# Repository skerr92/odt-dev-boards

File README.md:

# odt-dev-boards
repo for all the development boards for ODT

# Usage of Design Files

At Oak Development Technologies, we believe in open source hardware and software. To make this happen, we willingly publish the schematic and board files to 
all of our designs. With this in mind, we did take time to make these designs and share them with you and hope that you respect the MIT License we've attached herein to this repository.

Additionally, while we share these designs freely, making them isn't free. Purchasing these boards and designs from our store helps us continue to offer these designs free of charge.

Please help support the open source community and our contributions through sharing our mission with others and where possible, purchasing the hardware we cheerfully build for you

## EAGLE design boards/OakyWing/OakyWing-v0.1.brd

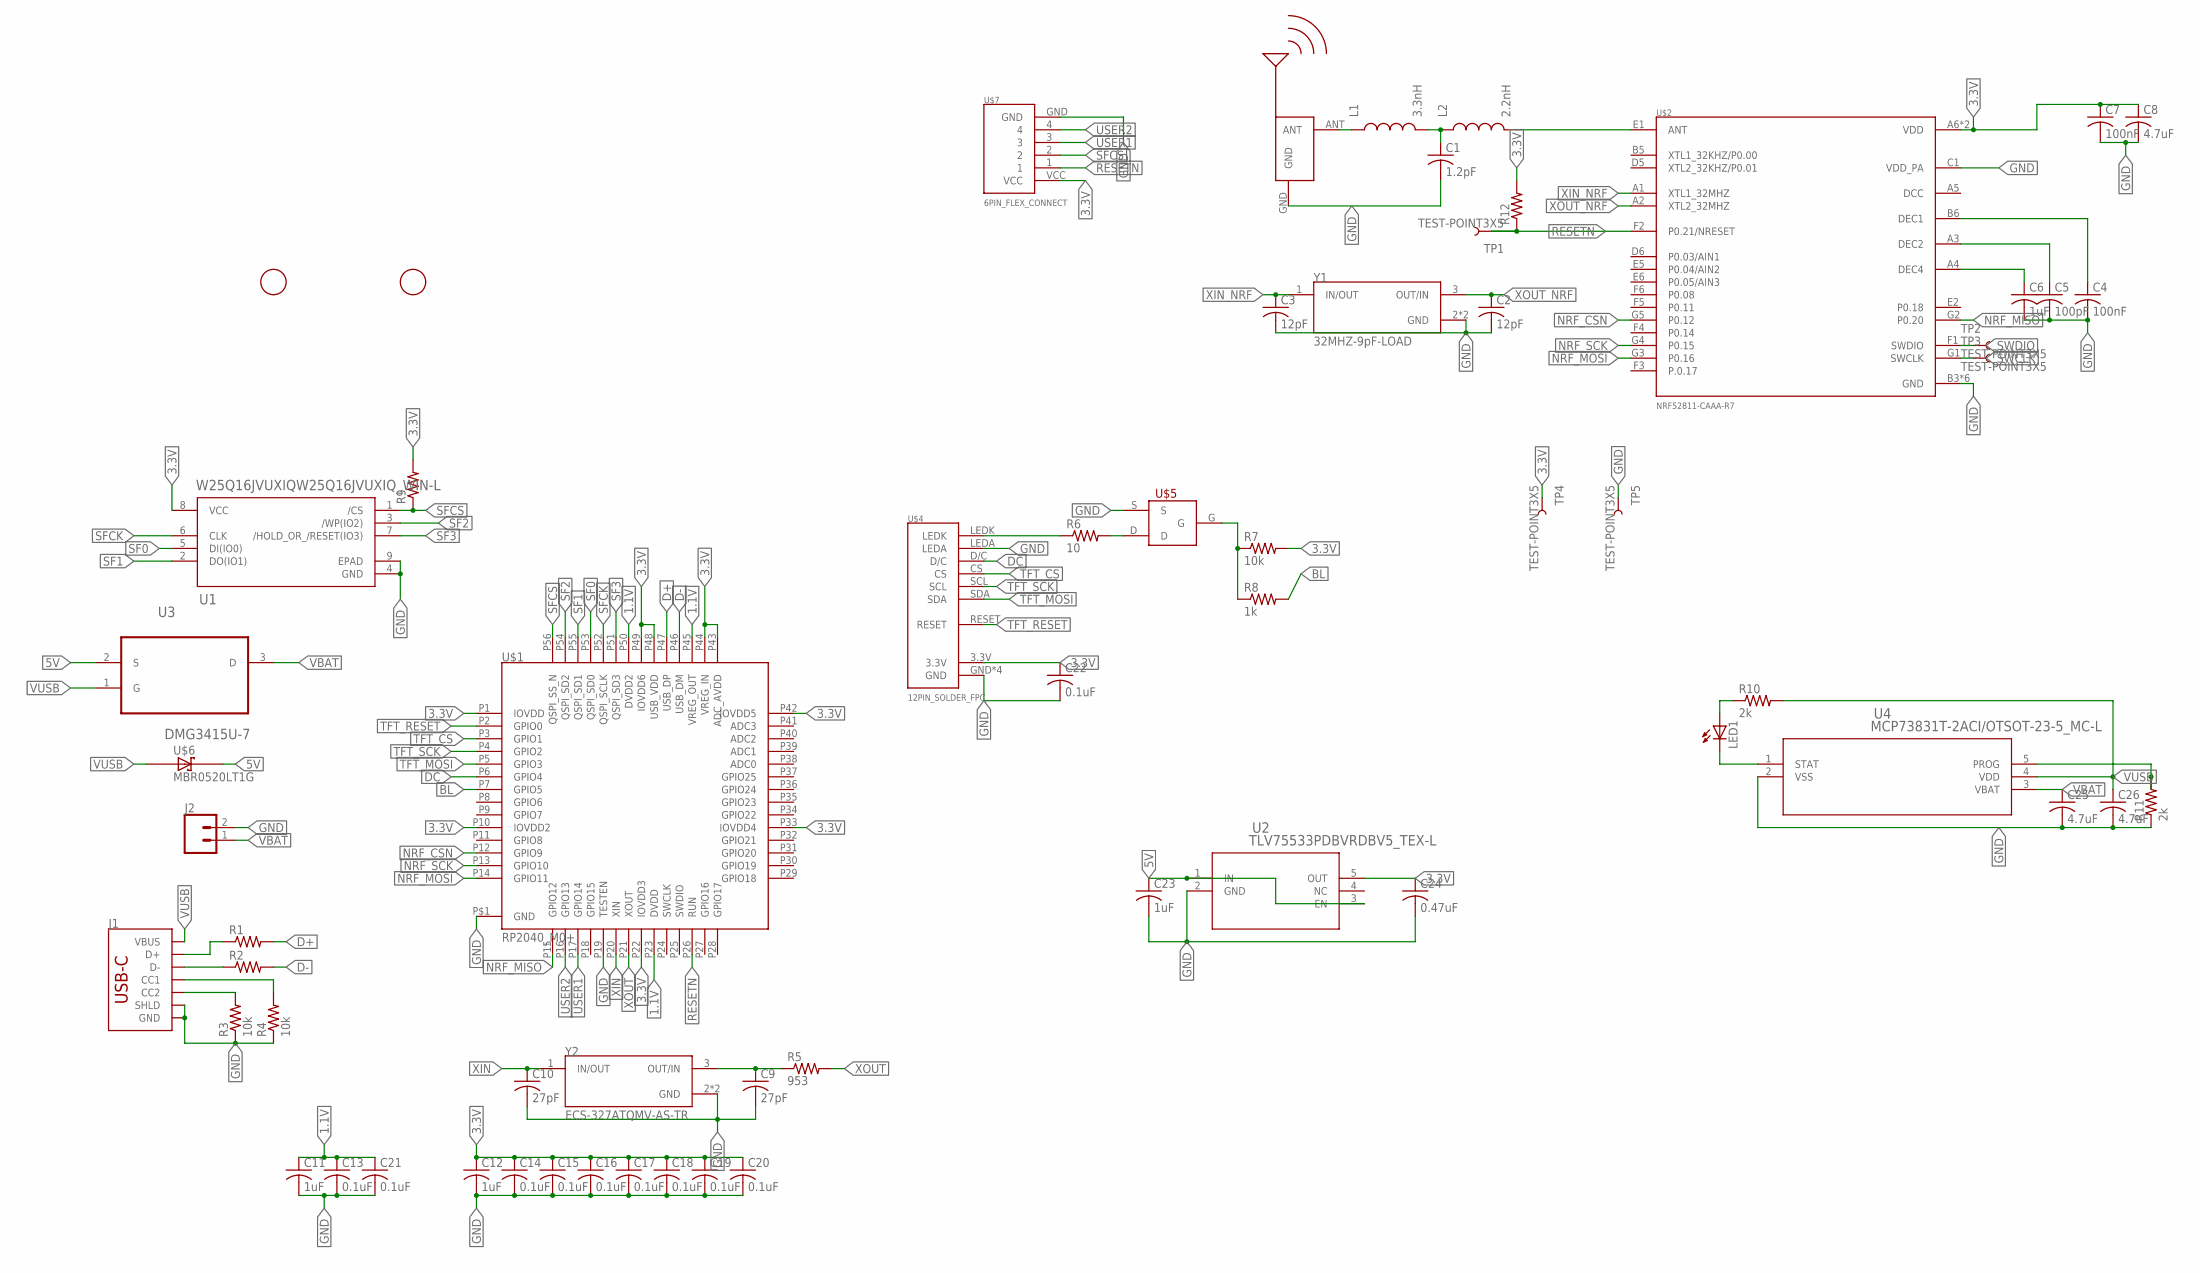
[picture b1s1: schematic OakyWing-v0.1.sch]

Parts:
C1: 1.2pF; C0402
C2, C3: 12pF; C0402
C4, C7: 100nF; C0402
C5: 100pF; C0402
C6, C11, C12, C23: 1uF; C0402
C8, C25, C26: 4.7uF; C0603
C9, C10: 27pF; C0402
C13, C14, C15, C16, C17, C18, C19, C20, C21, C22: 0.1uF; C0402
C24: 0.47uF; C0402
J1: USB_C_2-LAYER_PADS; USB-C-16P-2LAYER-PADS
J2: CONN_02; 1X02
L1: 3.3nH; R0402
L2: 2.2nH; R0402
LED1: LEDCHIP-LED0603; CHIP-LED0603
R1, R2: R-US_R0603; R0603
R3, R4, R7: 10k; R0402
R5: 953; R0402
R6: 10; R0402
R8: 1k; R0402
R9, R12: R-US_R0402; R0402
R10, R11: 2k; R0603
TP1, TP2, TP3, TP4, TP5: TEST-POINT3X5; PAD.03X.05
U1: W25Q16JVUXIQW25Q16JVUXIQ_WIN-L; W25Q16JVUXIQ_WIN-L
U2: TLV75533PDBVRDBV5_TEX-L; DBV5_TEX-L
U3: DMG3415U-7; SOT95P240X105-3N
U4: MCP73831T-2ACI/OTSOT-23-5_MC-L; SOT-23-5_MC-L
U$1: RP2040_M0+; QFN-56
U$2: NRF52811-CAAA-R7; WLCSP
U$3: BLE-2.45GHZ-ANTBLE-2.45GHZ-SERP-ANT; 2.45GHZ-SERPENTINE
U$4: 12PIN_SOLDER_FPC
U$5: DMN65D8L-7; SOT-23
U$6: MBR0520LT1G; SOD3716X117(SOD-123)
U$7: 6PIN_FLEX_CONNECT; 6PIN_0.7MM
U$8, U$9: FIDUCIAL; FIDUCIAL_1MM
Y1: 32MHZ-9pF-LOAD; XTAL_ECS-327ATQMV-AS-TR
Y2: ECS-327ATQMV-AS-TR; XTAL_ECS-327ATQMV-AS-TR

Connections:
1.1V: C11.1, C13.1, C21.1, U$1.P23 (DVDD), U$1.P45 (VREG_OUT), U$1.P50 (DVDD2)
3.3V: C7.1, C8.1, C12.1, C14.1, C15.1, C16.1, C17.1, C18.1, C19.1, C20.1, C22.1, C24.1, R7.2, R9.2, R12.2, TP4.P$1, U1.8 (VCC), U2.5 (OUT), U$1.P1 (IOVDD), U$1.P10 (IOVDD2), U$1.P22 (IOVDD3), U$1.P33 (IOVDD4), U$1.P42 (IOVDD5), U$1.P43 (ADC_AVDD), U$1.P44 (VREG_IN), U$1.P48 (USB_VDD), U$1.P49 (IOVDD6), U$2.A6 (VDD), U$2.G6 (VDD), U$4.3.3V, U$7.VCC
5V: C23.1, U2.1 (IN), U2.3 (EN), U3.2 (S), U$6.1 (C)
BL: R8.2, U$1.P7 (GPIO5)
D+: R1.2, U$1.P47 (USB_DP)
D-: R2.2, U$1.P46 (USB_DM)
DC: U$1.P6 (GPIO4), U$4.D/C
GND: C1.2, C2.2, C3.2, C4.2, C5.2, C6.2, C7.2, C8.2, C9.2, C10.2, C11.2, C12.2, C13.2, C14.2, C15.2, C16.2, C17.2, C18.2, C19.2, C20.2, C21.2, C22.2, C23.2, C24.2, C25.2, C26.2, J1.GND, J1.GND2 (GND), J1.P$1 (SHLD), J1.P$2 (SHLD), J1.P$3 (SHLD), J1.P$4 (SHLD), J1.SHLD1 (SHLD), J1.SHLD2 (SHLD), J1.SHLD3 (SHLD), J1.SHLD4 (SHLD), J2.2, R3.1, R4.1, R11.1, TP5.P$1, U1.4 (GND), U1.9 (EPAD), U2.2 (GND), U4.2 (VSS), U$1.P19 (TESTEN), U$1.P$1 (GND), U$2.B3 (GND), U$2.B4 (GND), U$2.C1 (VDD_PA), U$2.D3 (GND), U$2.D4 (GND), U$2.E3 (GND), U$2.E4 (GND), U$3.GND, U$4.GND, U$4.GND2 (GND), U$4.GND3 (GND), U$4.GND4 (GND), U$4.LEDA, U$5.S, U$7.GND, Y1.2 (GND), Y1.4 (GND), Y2.2 (GND), Y2.4 (GND)
unnamed: L2.2, U$2.E1 (ANT)
unnamed: C1.1, L1.2, L2.1
unnamed: L1.1, U$3.ANT
unnamed: C4.1, U$2.B6 (DEC1)
unnamed: C5.1, U$2.A3 (DEC2)
unnamed: C6.1, U$2.A4 (DEC4)
unnamed: C9.1, R5.1, Y2.3 (OUT/IN)
unnamed: J1.A6 (D+), J1.B6 (D+), R1.1
unnamed: J1.A7 (D-), J1.B7 (D-), R2.1
unnamed: J1.A5 (CC1), R4.2
unnamed: J1.B5 (CC2), R3.2
unnamed: R7.1, R8.1, U$5.G
unnamed: R6.2, U$5.D
unnamed: R6.1, U$4.LEDK
unnamed: LED1.C, U4.1 (STAT)
unnamed: R11.2, U4.5 (PROG)
unnamed: LED1.A, R10.1
NRF_CSN: U$1.P12 (GPIO9), U$2.G5 (P0.12)
NRF_MISO: U$1.P15 (GPIO12), U$2.G2 (P0.20)
NRF_MOSI: U$1.P14 (GPIO11), U$2.G3 (P0.16)
NRF_SCK: U$1.P13 (GPIO10), U$2.G4 (P0.15)
RESETN: R12.1, TP1.P$1, U$1.P26 (RUN), U$2.F2 (P0.21/NRESET), U$7.1
SF0: U1.5 (DI(IO0)), U$1.P53 (QSPI_SD0)
SF1: U1.2 (DO(IO1)), U$1.P55 (QSPI_SD1)
SF2: U1.3 (/WP(IO2)), U$1.P54 (QSPI_SD2)
SF3: U1.7 (/HOLD_OR_/RESET(IO3)), U$1.P51 (QSPI_SD3)
SFCK: U1.6 (CLK), U$1.P52 (QSPI_SCLK)
SFCS: R9.1, U1.1 (/CS), U$1.P56 (QSPI_SS_N), U$7.2
SWCLK: TP3.P$1, U$2.G1 (SWCLK)
SWDIO: TP2.P$1, U$2.F1 (SWDIO)
TFT_CS: U$1.P3 (GPIO1), U$4.CS
TFT_MOSI: U$1.P5 (GPIO3), U$4.SDA
TFT_RESET: U$1.P2 (GPIO0), U$4.RESET
TFT_SCK: U$1.P4 (GPIO2), U$4.SCL
USER1: U$1.P17 (GPIO14), U$7.3
USER2: U$1.P16 (GPIO13), U$7.4
VBAT: C25.1, J2.1, U3.3 (D), U4.3 (VBAT)
VUSB: C26.1, J1.VBUS1 (VBUS), J1.VBUS2 (VBUS), R10.2, U3.1 (G), U4.4 (VDD), U$6.2 (A)
XIN: C10.1, U$1.P20 (XIN), Y2.1 (IN/OUT)
XIN_NRF: C3.1, U$2.A1 (XTL1_32MHZ), Y1.1 (IN/OUT)
XOUT: R5.2, U$1.P21 (XOUT)
XOUT_NRF: C2.1, U$2.A2 (XTL2_32MHZ), Y1.3 (OUT/IN)

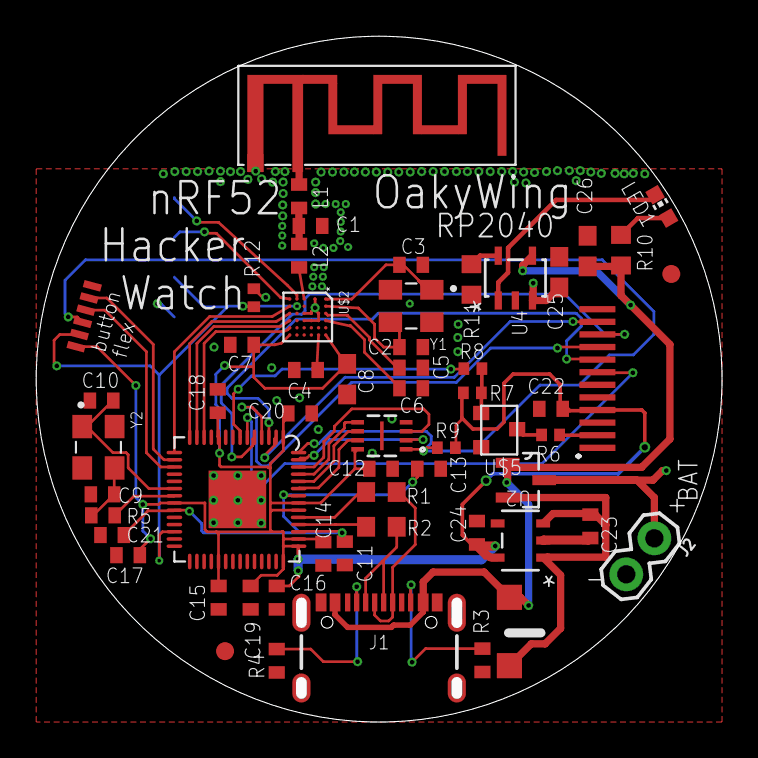
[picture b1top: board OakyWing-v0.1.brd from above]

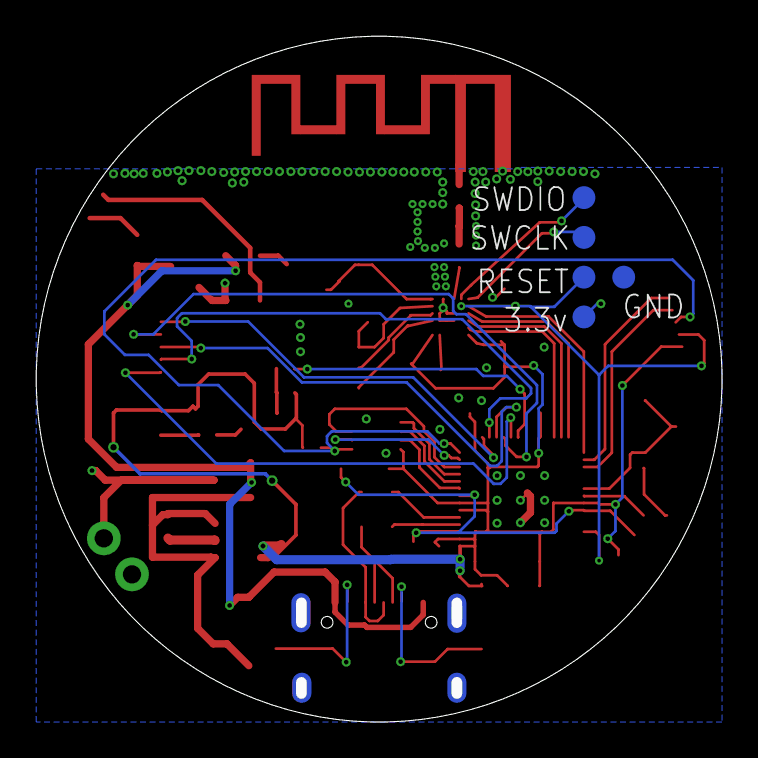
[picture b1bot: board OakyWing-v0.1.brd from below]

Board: 6 copper layers, 38.1 x 38.1 mm, 63 parts (5 on the bottom side), 50 nets.

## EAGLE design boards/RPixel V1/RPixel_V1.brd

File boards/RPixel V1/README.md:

# RPixel V1 Schematic and Board Files

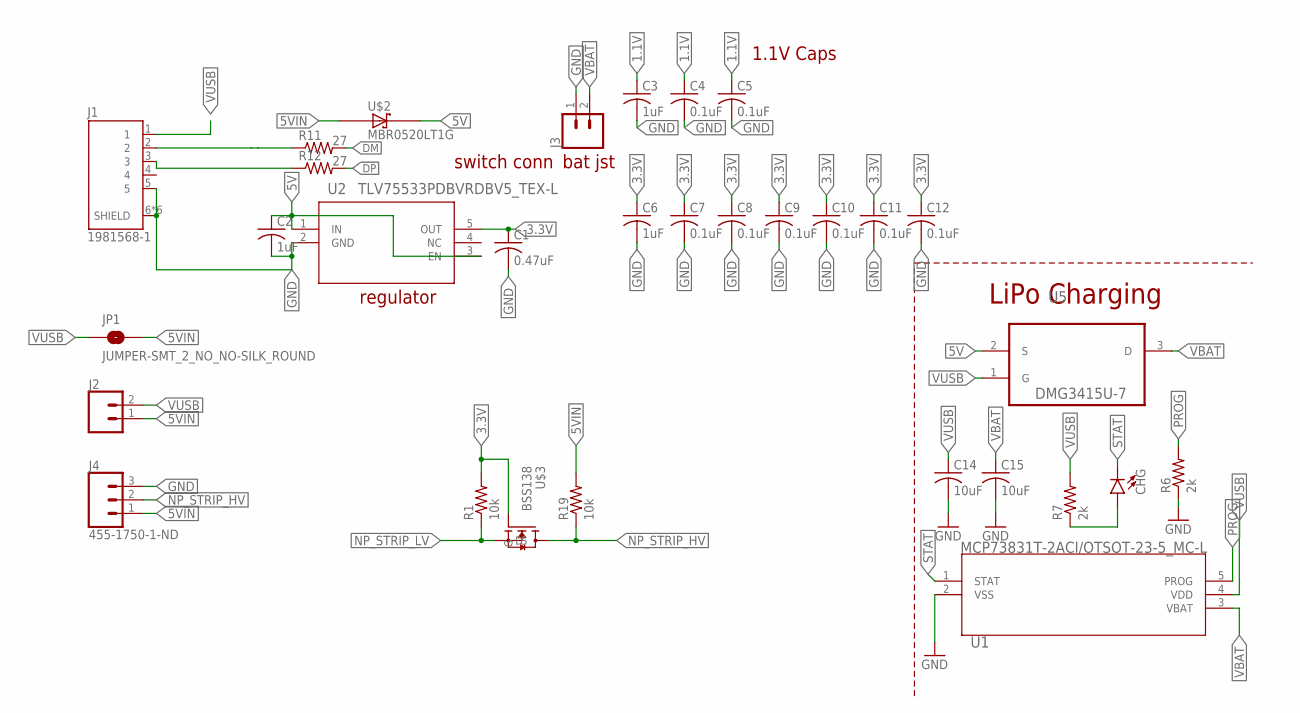
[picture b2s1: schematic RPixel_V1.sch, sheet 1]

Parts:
C1: 0.47uF; C0805
C2: 1uF; C0805
C3, C6: 1uF; C0402
C4, C5, C7, C8, C9, C10, C11, C12: 0.1uF; C0402
C14, C15: 10uF; C0603
CHG: LED0603; LED-0603
J1: 1981568-1; TE_1981568-1
J2: CONN_02; 1X02
J3: CONN_02-JST-2MM-SMT; JST-2-SMD
J4: 455-1750-1-ND; 1X03
JP1: JUMPER-SMT_2_NO_NO-SILK_ROUND; SMT-JUMPER_2_NO_NO-SILK_ROUND
R1, R19: 10k; R0603
R6, R7: 2k; R0603
R11, R12: 27; R0603
U1: MCP73831T-2ACI/OTSOT-23-5_MC-L; SOT-23-5_MC-L
U2: TLV75533PDBVRDBV5_TEX-L; DBV5_TEX-L
U5: DMG3415U-7; SOT95P240X105-3N
U$2: MBR0520LT1G; SOD3716X117(SOD-123)
U$3: BSS138

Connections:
1.1V: C3.1, C4.1, C5.1; also elsewhere on the board
3.3V: C1.1, C6.1, C7.1, C8.1, C9.1, C10.1, C11.1, C12.1, R1.2, U2.5 (OUT), U$3.G; also elsewhere on the board
5V: C2.1, U2.1 (IN), U2.3 (EN), U5.2 (S), U$2.1 (C)
5VIN: J2.1, J4.1, JP1.2, R19.2, U$2.2 (A)
DM: R11.2; also elsewhere on the board
DP: R12.2; also elsewhere on the board
GND: C1.2, C2.2, C3.2, C4.2, C5.2, C6.2, C7.2, C8.2, C9.2, C10.2, C11.2, C12.2, C14.2, C15.2, J1.5, J1.6 (SHIELD), J1.7 (SHIELD), J1.8 (SHIELD), J1.9 (SHIELD), J1.10 (SHIELD), J1.11 (SHIELD), J3.1 (2), J4.3, R6.1, U1.2 (VSS), U2.2 (GND); also elsewhere on the board
unnamed: CHG.A, R7.1
unnamed: J1.3, R12.1
unnamed: J1.2, R11.1
NP_STRIP_HV: J4.2, R19.1, U$3.D
NP_STRIP_LV: R1.1, U$3.S; also elsewhere on the board
PROG: R6.2, U1.5 (PROG)
STAT: CHG.C, U1.1 (STAT)
VBAT: C15.1, J3.2 (1), U1.3 (VBAT), U5.3 (D)
VUSB: C14.1, J1.1, J2.2, JP1.1, R7.2, U1.4 (VDD), U5.1 (G)

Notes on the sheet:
regulator
bat jst
switch conn
1.1V Caps
LiPo Charging

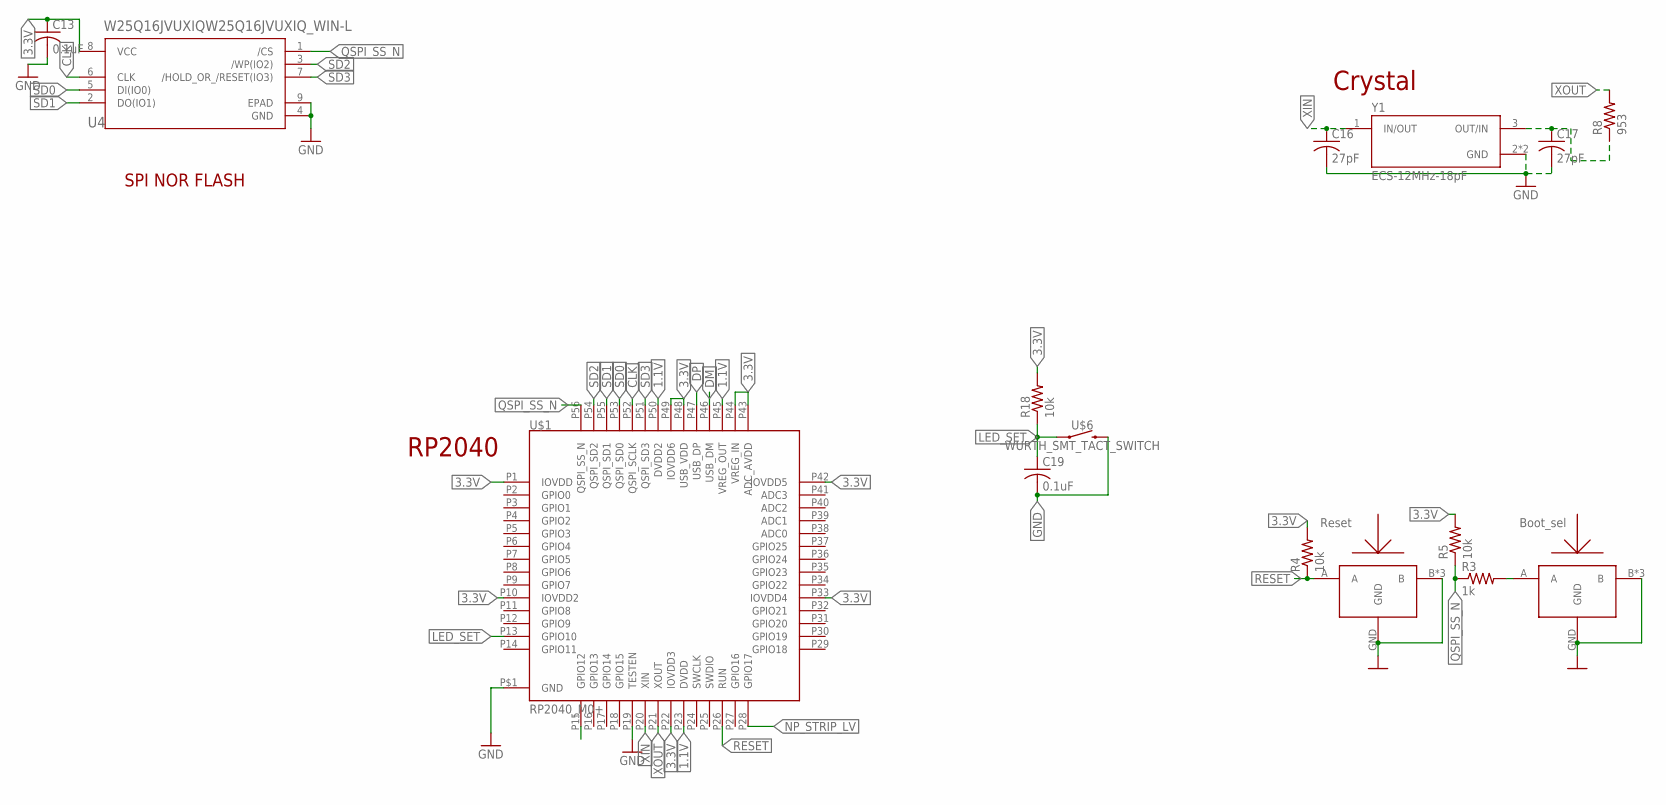
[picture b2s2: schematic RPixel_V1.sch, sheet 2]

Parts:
C13, C19: 0.1uF; C0402
C16, C17: 27pF; C0402
R3: 1k; R0402
R4, R5, R18: 10k; R0402
R8: 953; R0402
U4: W25Q16JVUXIQW25Q16JVUXIQ_WIN-L; W25Q16JVUXIQ_WIN-L
U$1: RP2040_M0+; QFN-56
U$4, U$5: SOF-232HST; 3.3X2.9
U$6: WURTH_SMT_TACT_SWITCH; SIDE_MOUNT_SWITCH
Y1: ECS-12MHz-18pF; XTAL_ECS-327ATQMV-AS-TR

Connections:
1.1V: U$1.P23 (DVDD), U$1.P45 (VREG_OUT), U$1.P50 (DVDD2); also elsewhere on the board
3.3V: C13.1, R4.2, R5.2, R18.2, U4.8 (VCC), U$1.P1 (IOVDD), U$1.P10 (IOVDD2), U$1.P22 (IOVDD3), U$1.P33 (IOVDD4), U$1.P42 (IOVDD5), U$1.P43 (ADC_AVDD), U$1.P44 (VREG_IN), U$1.P48 (USB_VDD), U$1.P49 (IOVDD6); also elsewhere on the board
CLK: U4.6 (CLK), U$1.P52 (QSPI_SCLK)
DM: U$1.P46 (USB_DM); also elsewhere on the board
DP: U$1.P47 (USB_DP); also elsewhere on the board
GND: C13.2, C16.2, C17.2, C19.2, U4.4 (GND), U4.9 (EPAD), U$1.P19 (TESTEN), U$1.P$1 (GND), U$4.B, U$4.B2 (B), U$4.B3 (B), U$4.GND, U$5.B, U$5.B2 (B), U$5.B3 (B), U$5.GND, U$6.2, Y1.2 (GND), Y1.4 (GND); also elsewhere on the board
LED_SET: C19.1, R18.1, U$1.P13 (GPIO10), U$6.1
unnamed: R3.2, U$5.A
unnamed: C17.1, R8.1, Y1.3 (OUT/IN)
NP_STRIP_LV: U$1.P28 (GPIO17); also elsewhere on the board
QSPI_SS_N: R3.1, R5.1, U4.1 (/CS), U$1.P56 (QSPI_SS_N)
RESET: R4.1, U$1.P26 (RUN), U$4.A
SD0: U4.5 (DI(IO0)), U$1.P53 (QSPI_SD0)
SD1: U4.2 (DO(IO1)), U$1.P55 (QSPI_SD1)
SD2: U4.3 (/WP(IO2)), U$1.P54 (QSPI_SD2)
SD3: U4.7 (/HOLD_OR_/RESET(IO3)), U$1.P51 (QSPI_SD3)
SDA: U$1.P15 (GPIO12)
XIN: C16.1, U$1.P20 (XIN), Y1.1 (IN/OUT)
XOUT: R8.2, U$1.P21 (XOUT)

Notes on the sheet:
RP2040
SPI NOR FLASH
Crystal
Reset
Boot_sel

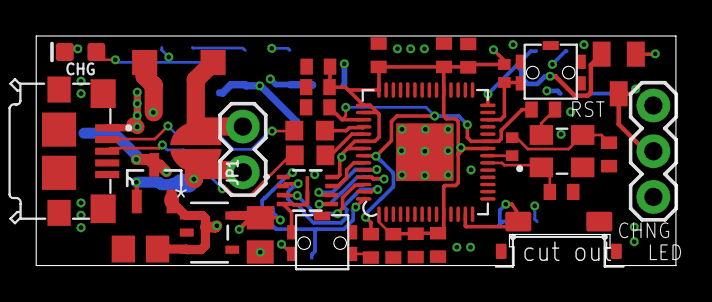
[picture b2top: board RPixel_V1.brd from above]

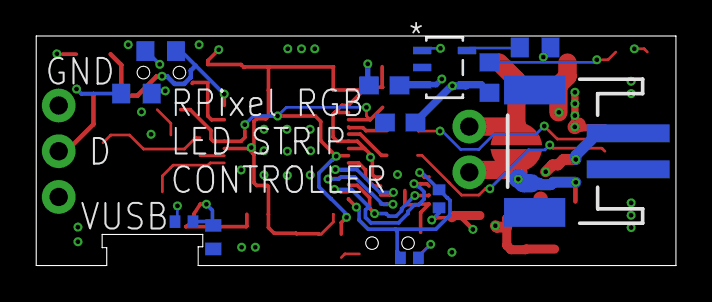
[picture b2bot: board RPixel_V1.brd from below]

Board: 4 copper layers, 35.5 x 12.7 mm, 46 parts (12 on the bottom side), 28 nets.

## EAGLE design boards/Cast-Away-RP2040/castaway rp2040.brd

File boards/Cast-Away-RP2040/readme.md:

# CAST-AWAY RP2040 design files

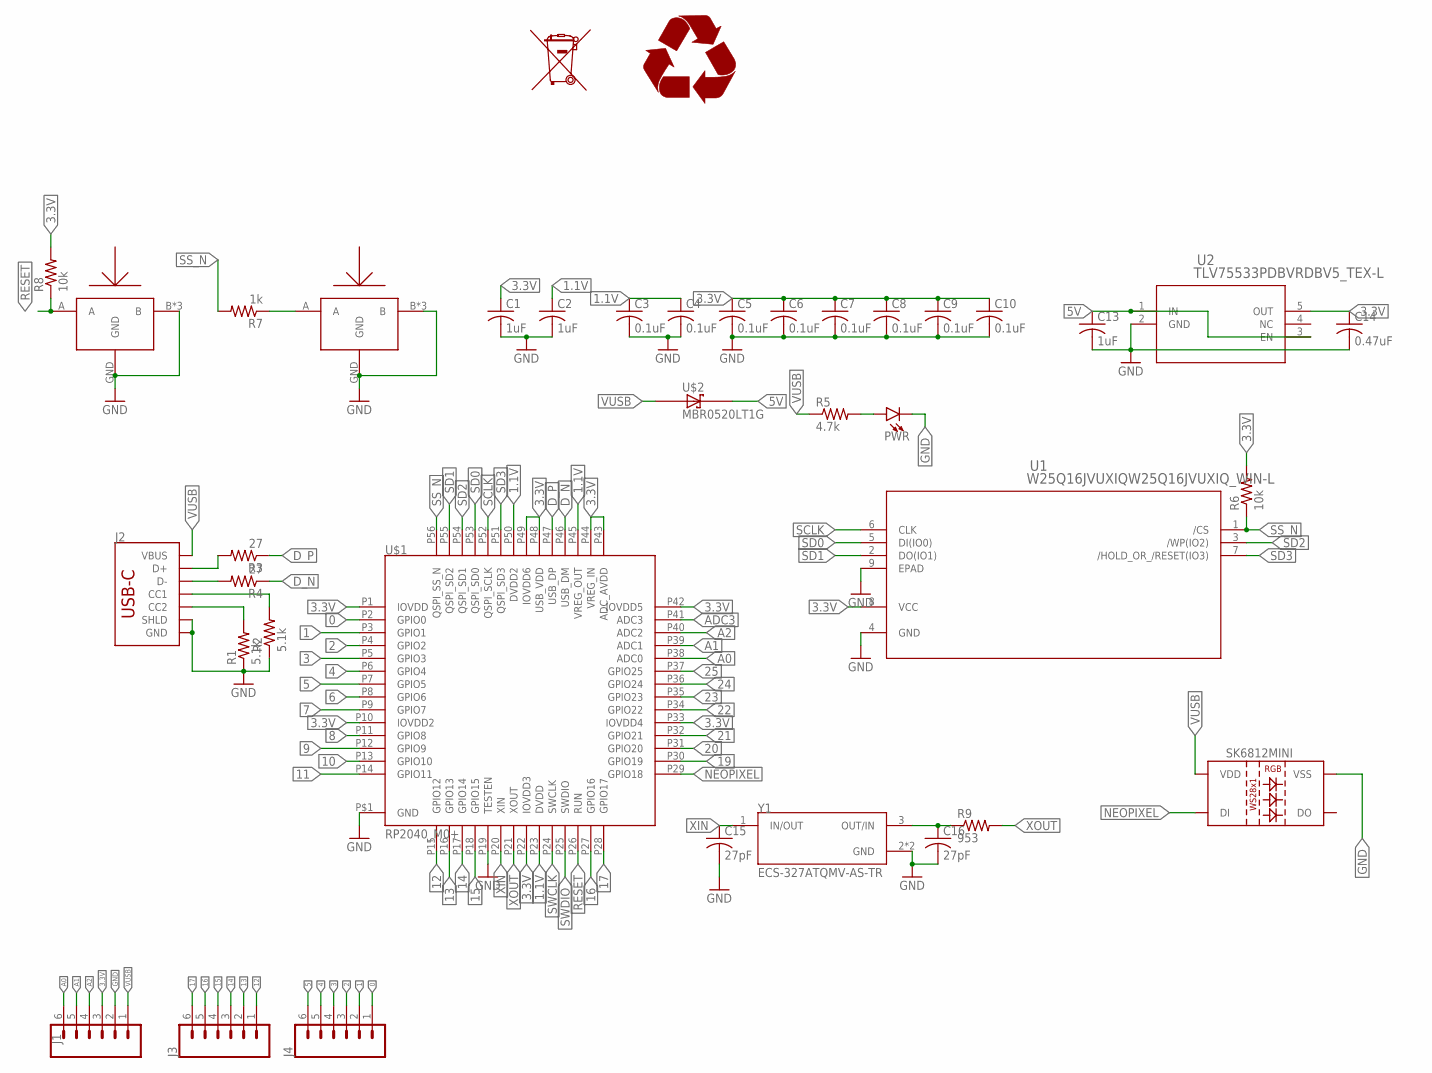
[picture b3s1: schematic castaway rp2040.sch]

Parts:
C1, C2, C13: 1uF; C0603
C3, C4, C5, C6, C7, C8, C9, C10: 0.1uF; C0603
C14: 0.47uF; C0603
C15, C16: 27pF; C0402
J1, J3, J4: CONN_06LONGPADS; 1X06_LONGPADS
J2: USB_C_2-LAYER_PADS; USB-C-16P-2LAYER-PADS
PWR: LED0603; LED-0603
R1, R2: 5.1k; R0603
R3, R4: 27; R0603
R5: 4.7k; R0603
R6, R8: 10k; R0603
R7: 1k; R0603
R9: 953; R0402
SK6812MINI: WS2812BWS2812B-3535; WS2812-3535
U1: W25Q16JVUXIQW25Q16JVUXIQ_WIN-L; W25Q16JVUXIQ_WIN-L
U2: TLV75533PDBVRDBV5_TEX-L; DBV5_TEX-L
U$1: RP2040_M0+; QFN-56
U$2: MBR0520LT1G; SOD3716X117(SOD-123)
U$3, U$4: SOF-232HST; 3.3X2.9
Y1: ECS-327ATQMV-AS-TR; XTAL_ECS-327ATQMV-AS-TR

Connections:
0: J4.1, U$1.P2 (GPIO0)
1: J4.2, U$1.P3 (GPIO1)
1.1V: C2.1, C3.1, C4.1, U$1.P23 (DVDD), U$1.P45 (VREG_OUT), U$1.P50 (DVDD2)
2: J4.3, U$1.P4 (GPIO2)
3: J4.4, U$1.P5 (GPIO3)
3.3V: C1.1, C5.1, C6.1, C7.1, C8.1, C9.1, C10.1, C14.1, J1.3, R6.2, R8.2, U1.8 (VCC), U2.5 (OUT), U$1.P1 (IOVDD), U$1.P10 (IOVDD2), U$1.P22 (IOVDD3), U$1.P33 (IOVDD4), U$1.P42 (IOVDD5), U$1.P43 (ADC_AVDD), U$1.P44 (VREG_IN), U$1.P48 (USB_VDD), U$1.P49 (IOVDD6)
4: J4.5, U$1.P6 (GPIO4)
5: J4.6, U$1.P7 (GPIO5)
5V: C13.1, U2.1 (IN), U2.3 (EN), U$2.1 (C)
6: U$1.P8 (GPIO6)
7: U$1.P9 (GPIO7)
8: U$1.P11 (GPIO8)
9: U$1.P12 (GPIO9)
10: U$1.P13 (GPIO10)
11: U$1.P14 (GPIO11)
12: J3.1, U$1.P15 (GPIO12)
13: J3.2, U$1.P16 (GPIO13)
14: J3.3, U$1.P17 (GPIO14)
15: J3.4, U$1.P18 (GPIO15)
16: J3.5, U$1.P27 (GPIO16)
17: J3.6, U$1.P28 (GPIO17)
19: U$1.P30 (GPIO19)
20: U$1.P31 (GPIO20)
21: U$1.P32 (GPIO21)
22: U$1.P34 (GPIO22)
23: U$1.P35 (GPIO23)
24: U$1.P36 (GPIO24)
25: U$1.P37 (GPIO25)
A0: J1.6, U$1.P38 (ADC0)
A1: J1.5, U$1.P39 (ADC1)
A2: J1.4, U$1.P40 (ADC2)
ADC3: U$1.P41 (ADC3)
D_N: R4.1, U$1.P46 (USB_DM)
D_P: R3.1, U$1.P47 (USB_DP)
GND: C1.2, C2.2, C3.2, C4.2, C5.2, C6.2, C7.2, C8.2, C9.2, C10.2, C13.2, C14.2, C15.2, C16.2, J1.2, J2.GND, J2.GND2 (GND), J2.P$1 (SHLD), J2.P$2 (SHLD), J2.P$3 (SHLD), J2.P$4 (SHLD), J2.SHLD1 (SHLD), J2.SHLD2 (SHLD), J2.SHLD3 (SHLD), J2.SHLD4 (SHLD), PWR.C, R1.1, R2.1, SK6812MINI.VSS, U1.4 (GND), U1.9 (EPAD), U2.2 (GND), U$1.P19 (TESTEN), U$1.P$1 (GND), U$3.B, U$3.B2 (B), U$3.B3 (B), U$3.GND, U$4.B, U$4.B2 (B), U$4.B3 (B), U$4.GND, Y1.2 (GND), Y1.4 (GND)
unnamed: PWR.A, R5.2
unnamed: J2.A5 (CC1), R2.2
unnamed: J2.B5 (CC2), R1.2
unnamed: C16.1, R9.1, Y1.3 (OUT/IN)
unnamed: R7.1, U$4.A
NEOPIXEL: SK6812MINI.DIN (DI), U$1.P29 (GPIO18)
RESET: R8.1, U$1.P26 (RUN), U$3.A
SCLK: U1.6 (CLK), U$1.P52 (QSPI_SCLK)
SD0: U1.5 (DI(IO0)), U$1.P53 (QSPI_SD0)
SD1: U1.2 (DO(IO1)), U$1.P55 (QSPI_SD2)
SD2: U1.3 (/WP(IO2)), U$1.P54 (QSPI_SD1)
SD3: U1.7 (/HOLD_OR_/RESET(IO3)), U$1.P51 (QSPI_SD3)
SS_N: R6.1, R7.2, U1.1 (/CS), U$1.P56 (QSPI_SS_N)
SWCLK: U$1.P24 (SWCLK)
SWDIO: U$1.P25 (SWDIO)
USB_N: J2.A7 (D-), J2.B7 (D-), R4.2
USB_P: J2.A6 (D+), J2.B6 (D+), R3.2
VUSB: J1.1, J2.VBUS1 (VBUS), J2.VBUS2 (VBUS), R5.1, SK6812MINI.VDD, U$2.2 (A)
XIN: C15.1, U$1.P20 (XIN), Y1.1 (IN/OUT)
XOUT: R9.2, U$1.P21 (XOUT)

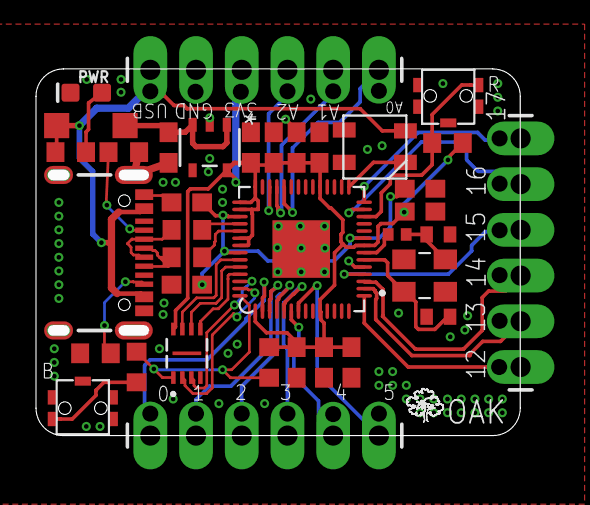
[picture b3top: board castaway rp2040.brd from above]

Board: 2 copper layers, 26.9 x 20.4 mm, 36 parts (0 on the bottom side), 39 nets.

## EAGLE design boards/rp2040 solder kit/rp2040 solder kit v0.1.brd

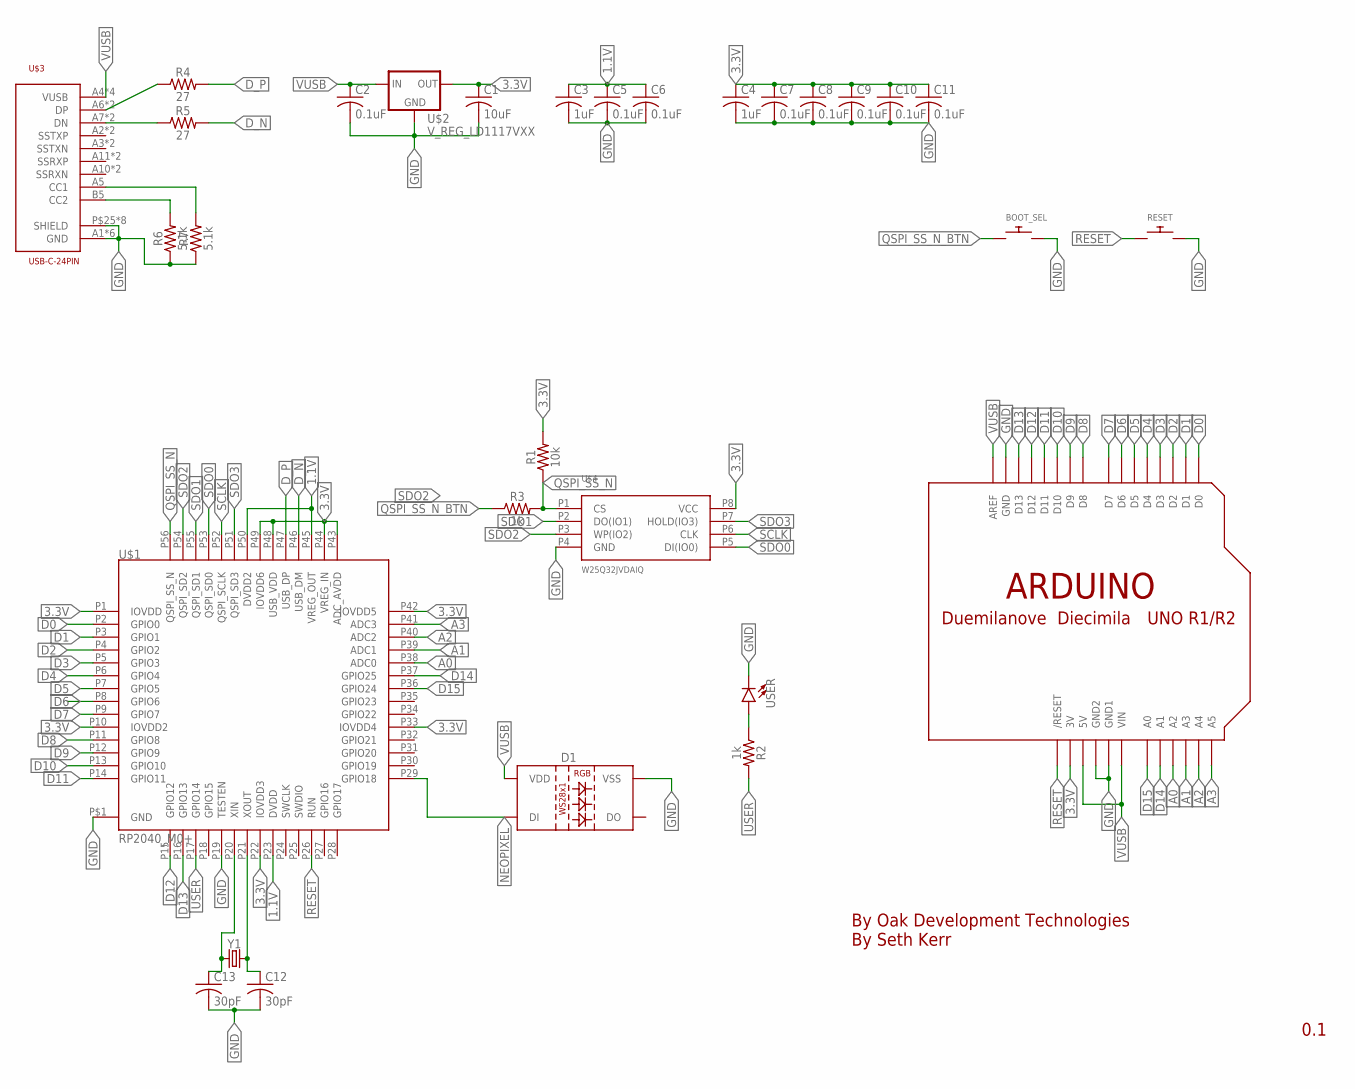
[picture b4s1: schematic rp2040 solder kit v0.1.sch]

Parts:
BOOT_SEL: SWITCH_PUSHBUTTONEVQ-PE; TACT_PANA-EVQ
C1: 10uF; C050-024X044
C2, C5, C6, C7, C8, C9, C10, C11: 0.1uF; C050-024X044
C3, C4: 1uF; C050-024X044
C12, C13: 30pF; C050-024X044
D1: WS2812BWS2812B-3535; WS2812-3535
R1: 10k; AXIAL-0.3
R2, R3: 1k; AXIAL-0.3
R4, R5: 27; AXIAL-0.3
R6, R7: 5.1k; AXIAL-0.3
RESET: SWITCH_PUSHBUTTONEVQ-PE; TACT_PANA-EVQ
U$1: RP2040_M0+; QFN-56
U$2: V_REG_LD1117VXX; 78XXL
U$3: USB-C-24PIN; USB-C-TH
U$4: W25Q32JVDAIQ; PDIP-8
U$5: ARDUINO-BPLACE
USER: LED-5MM-KIT-NO-SILK; LED_5MM-KIT-NO-SILK
Y1: CRYSTALPTH-HC49US; HC49US

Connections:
1.1V: C3.1, C5.1, C6.1, U$1.P23 (DVDD), U$1.P45 (VREG_OUT), U$1.P50 (DVDD2)
3.3V: C1.1, C4.1, C7.1, C8.1, C9.1, C10.1, C11.1, R1.P$2 (2), U$1.P1 (IOVDD), U$1.P10 (IOVDD2), U$1.P22 (IOVDD3), U$1.P33 (IOVDD4), U$1.P42 (IOVDD5), U$1.P43 (ADC_AVDD), U$1.P44 (VREG_IN), U$1.P48 (USB_VDD), U$1.P49 (IOVDD6), U$2.GND (OUT), U$4.P8 (VCC), U$5.3V
A0: U$1.P38 (ADC0), U$5.A2
A1: U$1.P39 (ADC1), U$5.A3
A2: U$1.P40 (ADC2), U$5.A4
A3: U$1.P41 (ADC3), U$5.A5
D0: U$1.P2 (GPIO0), U$5.D0
D1: U$1.P3 (GPIO1), U$5.D1
D2: U$1.P4 (GPIO2), U$5.D2
D3: U$1.P5 (GPIO3), U$5.D3
D4: U$1.P6 (GPIO4), U$5.D4
D5: U$1.P7 (GPIO5), U$5.D5
D6: U$1.P8 (GPIO6), U$5.D6
D7: U$1.P9 (GPIO7), U$5.D7
D8: U$1.P11 (GPIO8), U$5.D8
D9: U$1.P12 (GPIO9), U$5.D9
D10: U$1.P13 (GPIO10), U$5.D10
D11: U$1.P14 (GPIO11), U$5.D11
D12: U$1.P15 (GPIO12), U$5.D12
D13: U$1.P16 (GPIO13), U$5.D13
D14: U$1.P37 (GPIO25), U$5.A1
D15: U$1.P36 (GPIO24), U$5.A0
D_N: R5.P$2 (2), U$1.P46 (USB_DM)
D_P: R4.P$2 (2), U$1.P47 (USB_DP)
GND: BOOT_SEL.P$2, C1.2, C2.2, C3.2, C4.2, C5.2, C6.2, C7.2, C8.2, C9.2, C10.2, C11.2, C12.2, C13.2, D1.VSS, R6.P$1 (1), R7.P$1 (1), RESET.P$2, U$1.P19 (TESTEN), U$1.P$1 (GND), U$2.IN (GND), U$3.A1 (GND), U$3.A8 (GND), U$3.A12 (GND), U$3.B1 (GND), U$3.B8 (GND), U$3.B12 (GND), U$3.P$25 (SHIELD), U$3.P$26 (SHIELD), U$3.P$27 (SHIELD), U$3.P$28 (SHIELD), U$3.P$29 (SHIELD), U$3.P$30 (SHIELD), U$3.P$31 (SHIELD), U$3.P$32 (SHIELD), U$4.P4 (GND), U$5.GND, U$5.GND1, U$5.GND2, USER.K (C)
unnamed: R7.P$2 (2), U$3.A5 (CC1)
unnamed: R6.P$2 (2), U$3.B5 (CC2)
unnamed: C12.1, U$1.P21 (XOUT), Y1.2
unnamed: R4.P$1 (1), U$3.A6 (DP), U$3.B6 (DP)
unnamed: R5.P$1 (1), U$3.A7 (DN), U$3.B7 (DN)
unnamed: R2.P$1 (1), USER.A
unnamed: C13.1, U$1.P20 (XIN), Y1.1
NEOPIXEL: D1.DIN (DI), U$1.P29 (GPIO18)
QSPI_SS_N: R1.P$1 (1), R3.P$2 (2), U$1.P56 (QSPI_SS_N), U$4.P1 (CS)
QSPI_SS_N_BTN: BOOT_SEL.P$1, R3.P$1 (1)
RESET: RESET.P$1, U$1.P26 (RUN), U$5.RESET (/RESET)
SCLK: U$1.P52 (QSPI_SCLK), U$4.P6 (CLK)
SDO0: U$1.P53 (QSPI_SD0), U$4.P5 (DI(IO0))
SDO1: U$1.P55 (QSPI_SD1), U$4.P2 (DO(IO1))
SDO2: U$1.P54 (QSPI_SD2), U$4.P3 (WP(IO2))
SDO3: U$1.P51 (QSPI_SD3), U$4.P7 (HOLD(IO3))
USER: R2.P$2 (2), U$1.P17 (GPIO14)
VUSB: C2.1, D1.VDD, U$2.OUT (IN), U$3.A4 (VUSB), U$3.A9 (VUSB), U$3.B4 (VUSB), U$3.B9 (VUSB), U$5.5V, U$5.AREF, U$5.VIN

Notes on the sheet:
0.1
By Oak Development Technologies By Seth Kerr

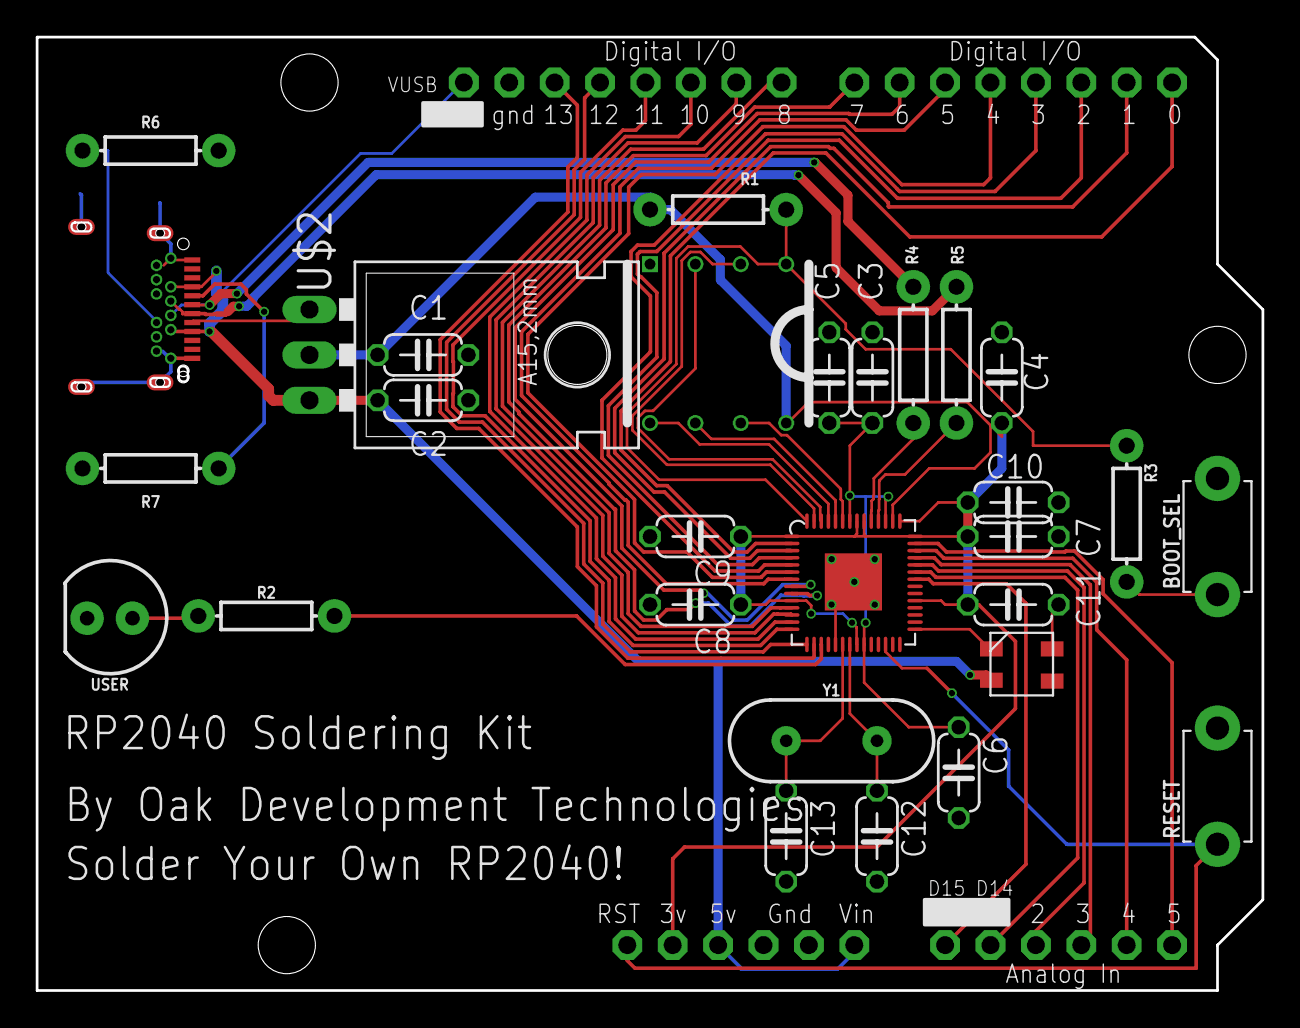
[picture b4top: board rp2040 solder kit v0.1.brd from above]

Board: 2 copper layers, 68.6 x 53.3 mm, 30 parts (0 on the bottom side), 43 nets.

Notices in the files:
parts and their libraries:
SparkFun-LED: Licensing: Creative Commons ShareAlike 4.0 International - https://creativecommons.org/licenses/by-sa/4.0
COPYRIGHT: Copyright (C) 2018 Accelerated Designs. All rights reserved
